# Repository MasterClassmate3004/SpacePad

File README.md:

B2 BomboPad is a custom six-key macropad with two rotary encoders, designed and built from scratch.

Its angular PCB and enclosure are inspired by the silhouette of the B-2 Spirit stealth bomber. The design combines a functional macropad with an aircraft-inspired industrial aesthetic.

## Features

- 6 mechanical keys
- 2 rotary encoders with push switches
- Seeed Studio XIAO RP2040 microcontroller
- 2 × 3 diode key matrix
- Custom PCB designed in KiCad
- Custom top and bottom enclosure designed in Onshape
- QMK firmware
- Gerber files included for PCB fabrication

## Key Layout

```text
        W

     A  S  D

       ↑  ↓
```

## Bills of Materials

- 1x Seeed XIAO RP2040
- 6x MX-Style Switches
- 6x White Blank DSA keycaps
- 6x through hole 1N4148 Diodes
- 2x EC11E Rotary Encoders

## Images

### PCB

### CAD

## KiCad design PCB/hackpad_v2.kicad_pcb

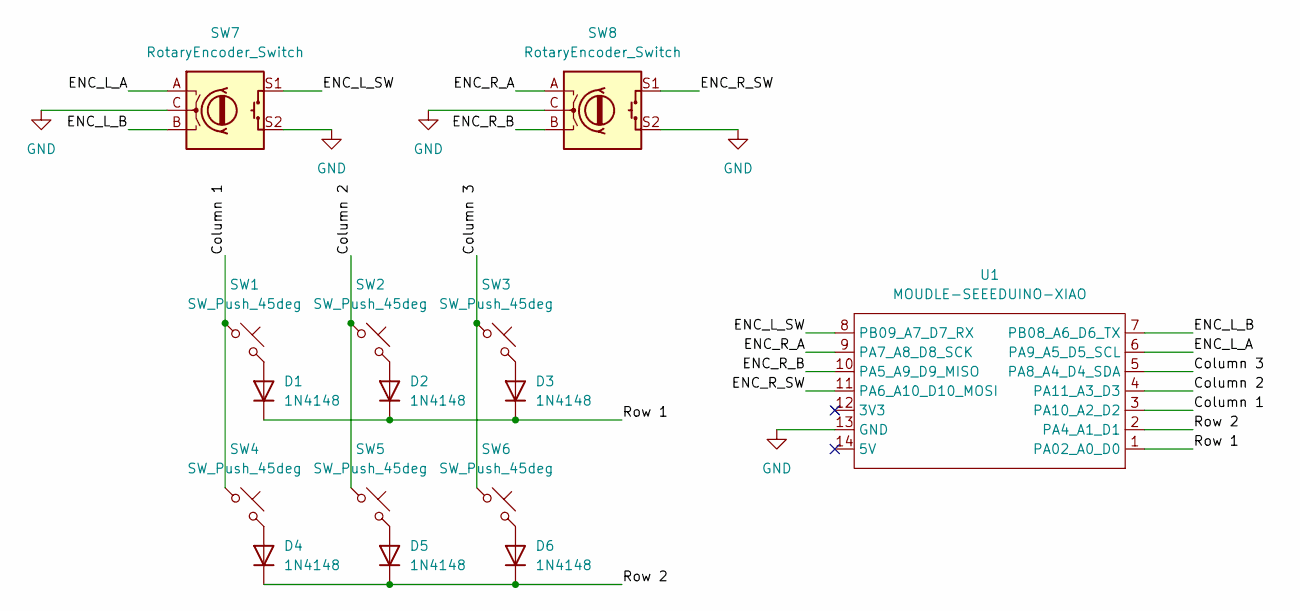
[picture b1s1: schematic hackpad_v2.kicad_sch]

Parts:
D1, D2, D3, D4, D5, D6: 1N4148; D_DO-35_SOD27_P7.62mm_Horizontal
SW1, SW2, SW3, SW4, SW5, SW6: SW_Push_45deg; SW_Cherry_MX_1.00u_PCB
SW7, SW8: RotaryEncoder_Switch; RotaryEncoder_Alps_EC11E-Switch_Vertical_H20mm
U1: MOUDLE-SEEEDUINO-XIAO; XIAO-Generic-Hybrid-14P-2.54-21X17.8MM

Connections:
/Column 1: SW1.1, SW4.1, U1.3 (PA10_A2_D2)
/Column 2: SW2.1, SW5.1, U1.4 (PA11_A3_D3)
/Column 3: SW3.1, SW6.1, U1.5 (PA8_A4_D4_SDA)
/ENC_L_A: SW7.A, U1.6 (PA9_A5_D5_SCL)
/ENC_L_B: SW7.B, U1.7 (PB08_A6_D6_TX)
/ENC_L_SW: SW7.S1, U1.8 (PB09_A7_D7_RX)
/ENC_R_A: SW8.A, U1.9 (PA7_A8_D8_SCK)
/ENC_R_B: SW8.B, U1.10 (PA5_A9_D9_MISO)
/ENC_R_SW: SW8.S1, U1.11 (PA6_A10_D10_MOSI)
/Row 1: D1.1 (K), D2.1 (K), D3.1 (K), U1.1 (PA02_A0_D0)
/Row 2: D4.1 (K), D5.1 (K), D6.1 (K), U1.2 (PA4_A1_D1)
GND: SW7.C, SW7.S2, SW8.C, SW8.S2, U1.13 (GND)
unnamed: D1.2 (A), SW1.2
unnamed: D2.2 (A), SW2.2
unnamed: D3.2 (A), SW3.2
unnamed: D4.2 (A), SW4.2
unnamed: D5.2 (A), SW5.2
unnamed: D6.2 (A), SW6.2

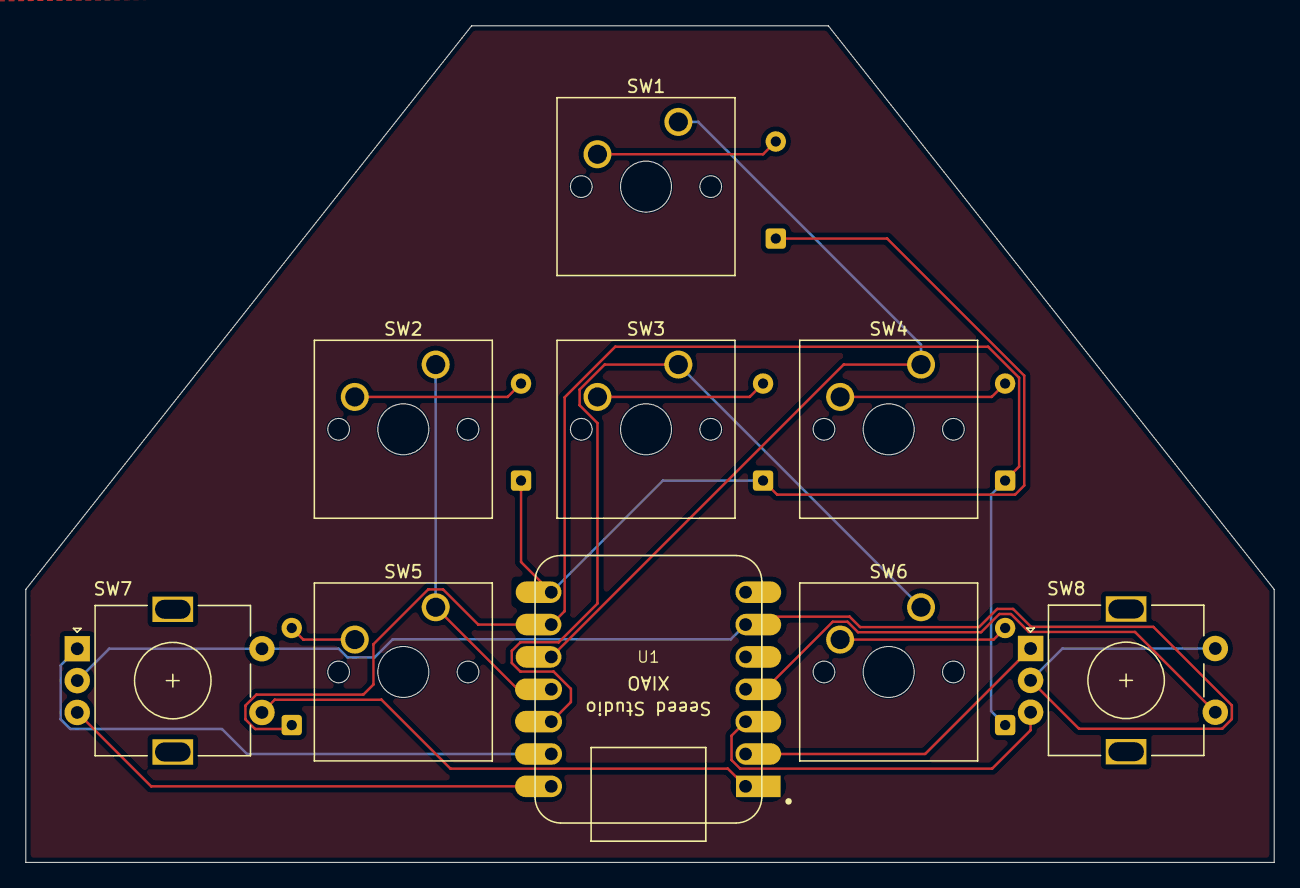
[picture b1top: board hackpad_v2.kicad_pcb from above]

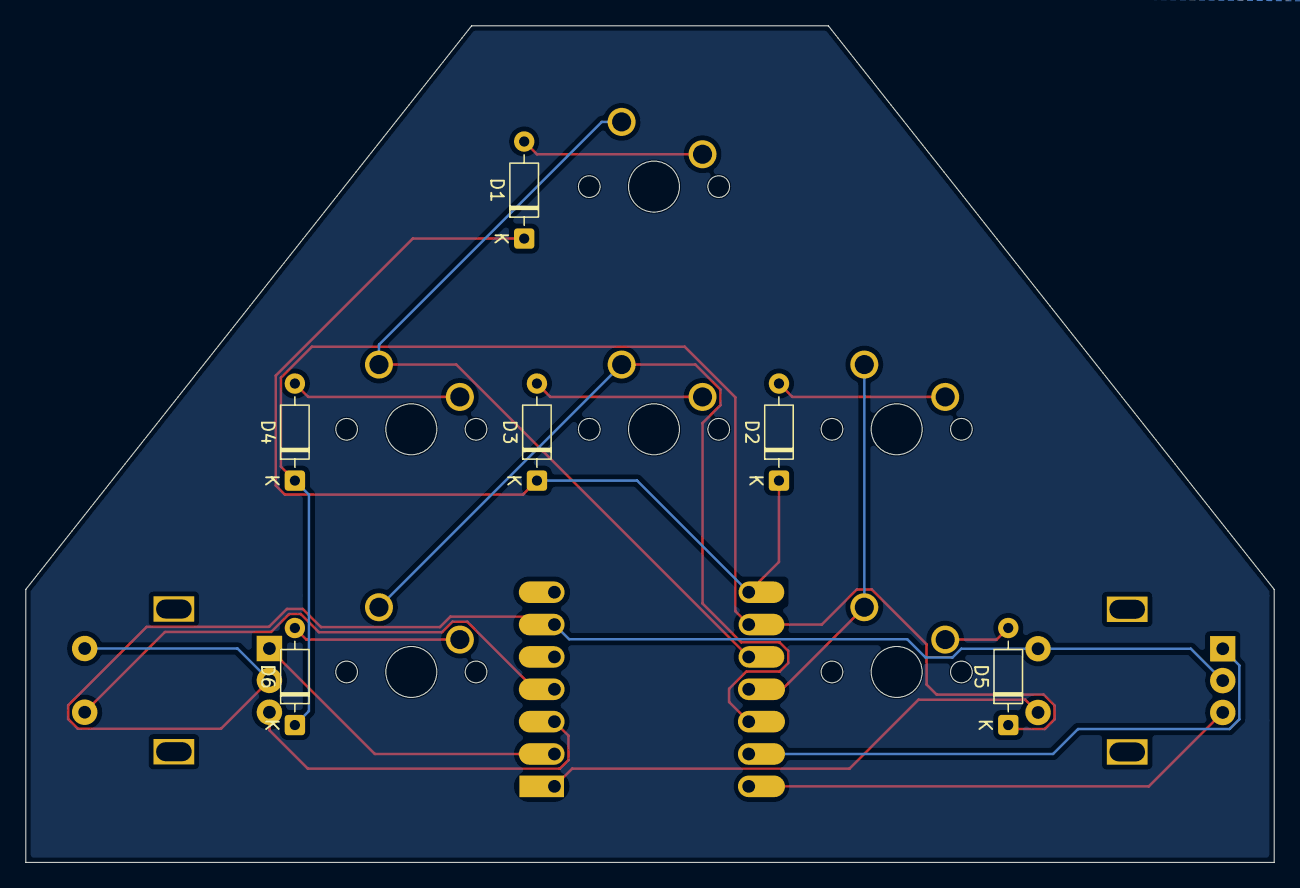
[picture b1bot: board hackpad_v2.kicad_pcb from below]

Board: 2 copper layers, 98.0 x 65.7 mm, 15 parts (6 on the bottom side), 18 nets.
